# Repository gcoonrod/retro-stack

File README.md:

# retro-stack

A retro computer project based on stackable PCB boards. This project was largely inspired by Ben Eater's 6502 breadboard computer project.

## Project Objective

Design, prototype, and build an 8 bit computer roughly comparable to an Apple II or NES in capabilities.

### Hardware Design Goals

Create an 8 bit computer with the following basic capabilities:

- Stable at or near maximum frequency of the processor
- Modular (including reconfigurable address map)
- Character display via RS-232 Serial and LCD
- PS/2 Keyboard Input

Optional:

- Sound generation
- VGA video output
- 10baseT ethernet

### Software Design Goals

- Develop a strong understanding of Assembly programming
- Understand and implement the following protocols:
  - UART
  - SPI
  - PS/2
- Learn the basics of PLDs and CUPL to use in "glue logic"
- Develop a moderate to strong understanding of Atmel AVR MCU programming
- Implement a simple Operating System within the constraints of an 8 bit architecture
- Understand and implement both software and hardware interrupts

## Repository Layout

This repository contains all of the hardware and software assets in the following structure:

- [Hardware Schematics and PCB Layouts](./boards/)
- [Firmware](./firmware/)
- Tooling (TBD)
- Documentation (TBD)s

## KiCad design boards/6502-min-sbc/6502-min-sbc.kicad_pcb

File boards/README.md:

<!--
 Copyright 2023 Greg Coonrod
 
 Licensed under the Apache License, Version 2.0 (the "License");
 you may not use this file except in compliance with the License.
 You may obtain a copy of the License at
 
     http://www.apache.org/licenses/LICENSE-2.0
 
 Unless required by applicable law or agreed to in writing, software
 distributed under the License is distributed on an "AS IS" BASIS,
 WITHOUT WARRANTIES OR CONDITIONS OF ANY KIND, either express or implied.
 See the License for the specific language governing permissions and
 limitations under the License.
-->

# RetroStack - Boards

The RetroStack project currently includes the following boards based on a common [template](./retro-stack-template/):

- [Power Supply & 555 Clock](./retro-stack-power-clock/)
- [W65C02S CPU & High Speed Clock](./retro-stack-cpu/)
- [SRAM & ROM](./retro-stack-ram-rom/)
- [Arduino Mega Debug Shield](./retro-stack-debug-arduino-mega-shield/)
- [Debug & Status Display](./retro-stack-debug/)

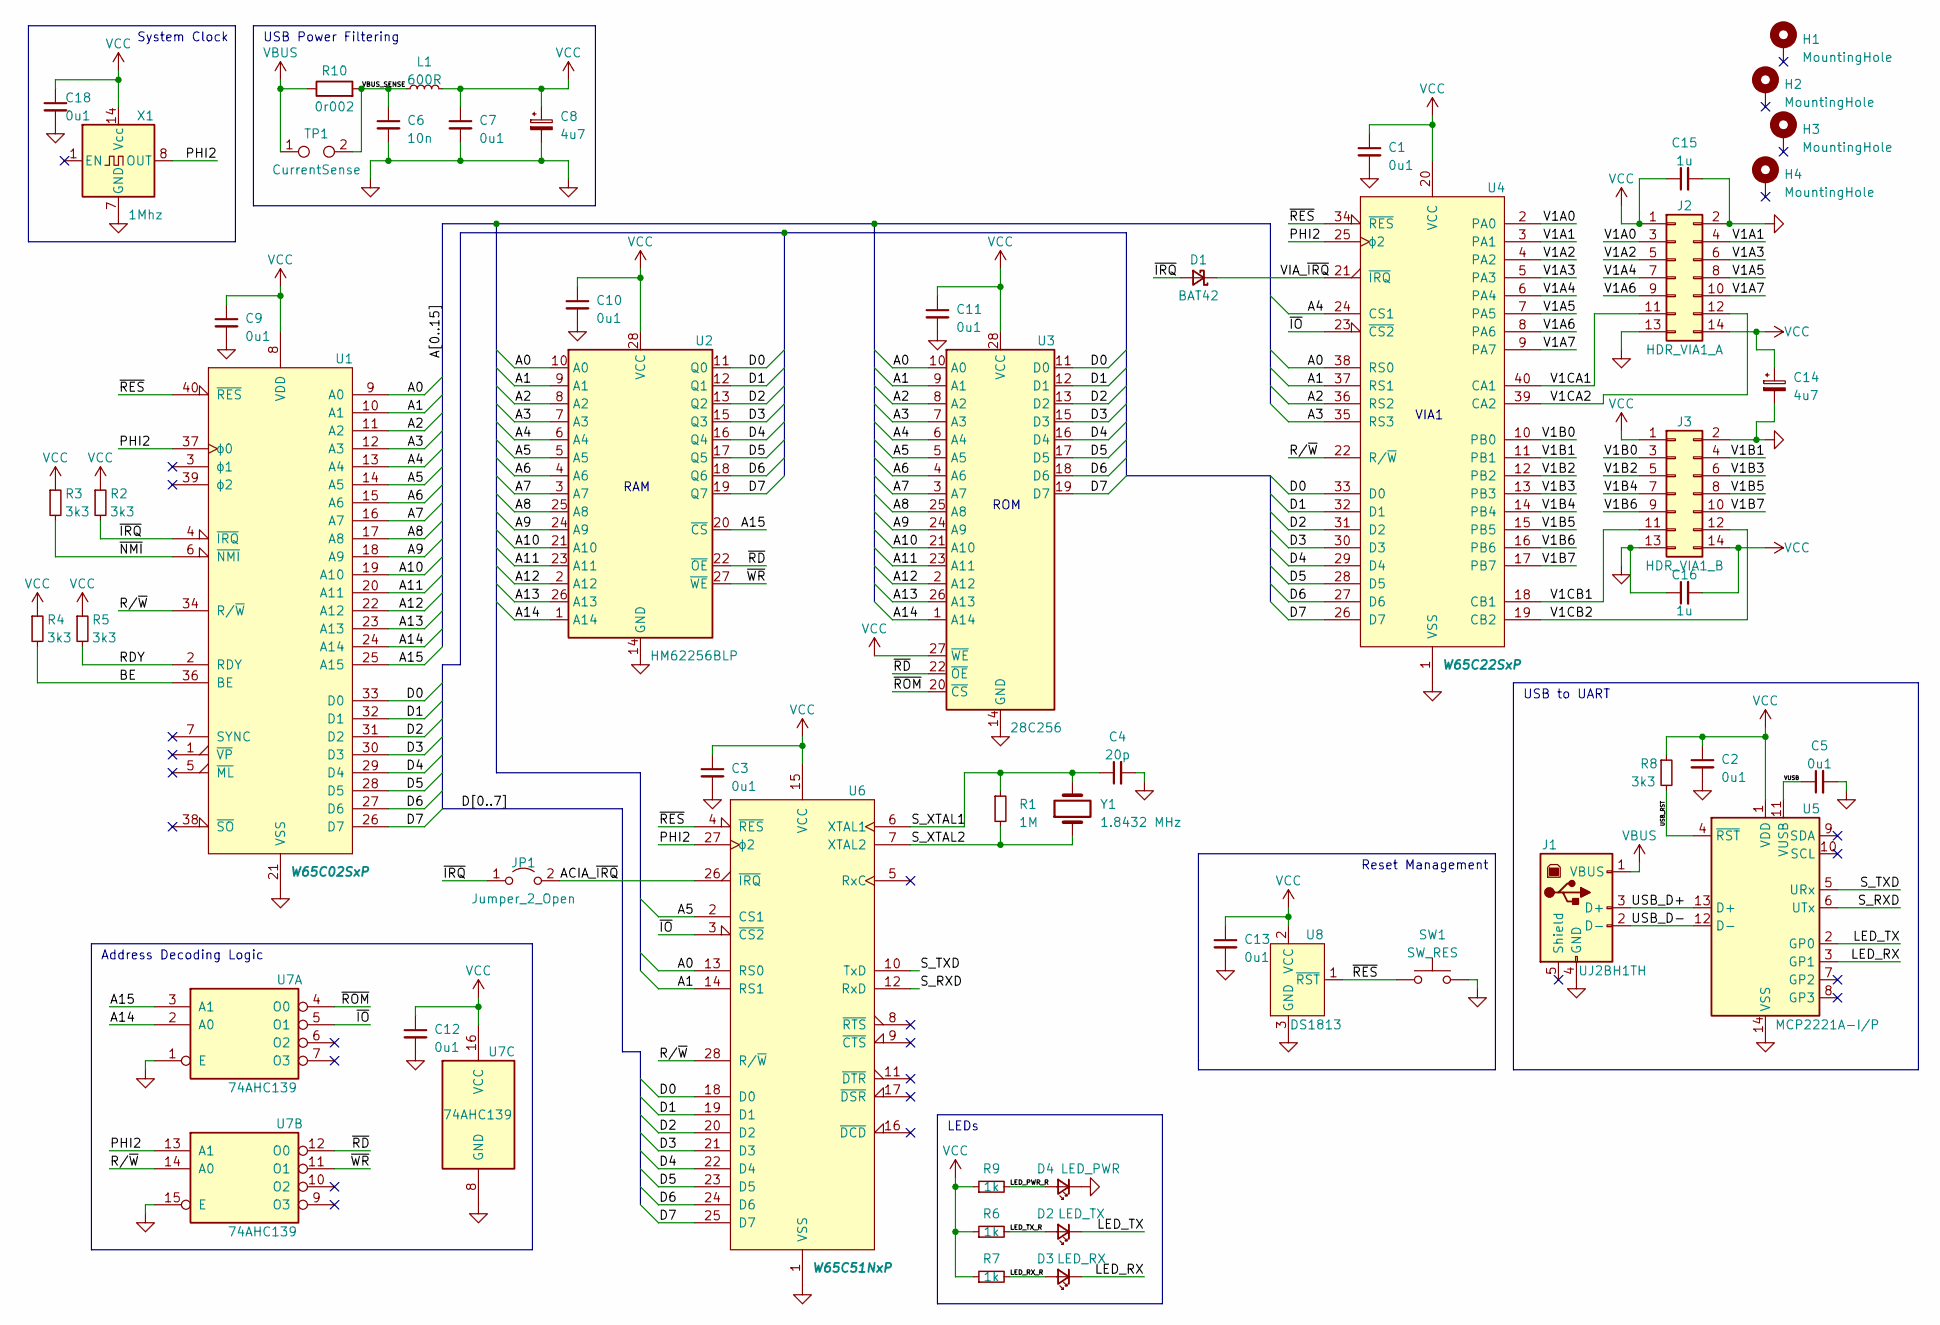
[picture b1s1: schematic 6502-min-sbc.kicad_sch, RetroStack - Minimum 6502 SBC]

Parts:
C1, C2, C3, C5, C7, C9, C10, C11, C12, C13, C18: 0u1; C_Rect_L4.0mm_W2.5mm_P2.50mm; Manufacturer Part K104K15X7RF5TL2
C4: 20p; C_Rect_L4.6mm_W3.8mm_P2.50mm_MKS02_FKP02; Manufacturer Part C315C200J3G5TA
C6: 10n; C_Rect_L4.0mm_W2.5mm_P2.50mm; Manufacturer Part K103K10X7RF53L2
C8, C14: 4u7; CP_Radial_D5.0mm_P2.50mm; Manufacturer Part ECE-A1VKS4R7I
C15, C16: 1u; C_Rect_L4.6mm_W3.0mm_P2.50mm_MKS02_FKP02; Manufacturer Part FG18X7R1E105KRT06
D1: BAT42; D_DO-35_SOD27_P7.62mm_Horizontal; Manufacturer Part BAT42
D2: LED_TX; LED_D5.0mm; Manufacturer Part WP7113YT
D3: LED_RX; LED_D5.0mm; Manufacturer Part WP7113YT
D4: LED_PWR; LED_D5.0mm; Manufacturer Part WP7113YT
H1, H2, H3, H4: MountingHole; MountingHole_3.2mm_M3_Pad
J1: UJ2BH1TH; Manufacturer Part UJ2-BH-1-TH
J2: HDR_VIA1_A; IDC-Header_2x07_P2.54mm_Vertical; Manufacturer Part 61201421621
J3: HDR_VIA1_B; IDC-Header_2x07_P2.54mm_Vertical; Manufacturer Part 61201421621
JP1: Jumper_2_Open; PinHeader_1x02_P2.54mm_Vertical
L1: 600R; LairdTech_28C0236-0JW-10; Manufacturer Part 28C0236-0JW-10
R1: 1M; R_Axial_DIN0204_L3.6mm_D1.6mm_P5.08mm_Horizontal; Manufacturer Part MBA02040C1004FCT00
R2, R3, R4, R5, R8: 3k3; R_Axial_DIN0204_L3.6mm_D1.6mm_P5.08mm_Horizontal; Manufacturer Part MBA02040C3301FCT00
R6, R7, R9: 1k; R_Axial_DIN0204_L3.6mm_D1.6mm_P5.08mm_Horizontal; Manufacturer Part MBA02040C1001FCT00
R10: 0r002; RESC6430X38N; Manufacturer Part WSLF25122L000FEA
SW1: SW_RES; SW_PUSH_6mm
TP1: CurrentSense; TestPoint_2Pads_Pitch2.54mm_Drill0.8mm
U1: W65C02SxP; DIP-40_W15.24mm_Socket_LongPads; Manufacturer Part W65C02S6TPG-14
U2: HM62256BLP; DIP-28_W15.24mm_Socket_LongPads; Manufacturer Part AS6C62256-55PCN
U3: 28C256; 28655410; Manufacturer Part AT28C256-15PU
U4: W65C22SxP; DIP-40_W15.24mm_Socket_LongPads; Manufacturer Part W65C22S6TPG-14
U5: MCP2221A-I/P; DIP-14_W7.62mm_Socket_LongPads; Manufacturer Part MCP2221A-I/P
U6: W65C51NxP; DIP-28_W15.24mm_Socket_LongPads; Manufacturer Part W65C51N6TPG-14
U7: 74AHC139; DIP-16_W7.62mm_Socket_LongPads; Manufacturer Part SN74AHC139N
U8: DS1813; TO-92; Manufacturer Part DS1813-15+
X1: 1Mhz; Oscillator_DIP-14; Manufacturer Part MXO45T-2C-1M0000
Y1: 1.8432 MHz; Crystal_HC49-U_Vertical; Manufacturer Part AB-1.8432MHZ-B2

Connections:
/A0: U1.9 (A0), U2.10 (A0), U3.10 (A0), U4.38 (RS0), U6.13 (RS0)
/A1: U1.10 (A1), U2.9 (A1), U3.9 (A1), U4.37 (RS1), U6.14 (RS1)
/A2: U1.11 (A2), U2.8 (A2), U3.8 (A2), U4.36 (RS2)
/A3: U1.12 (A3), U2.7 (A3), U3.7 (A3), U4.35 (RS3)
/A4: U1.13 (A4), U2.6 (A4), U3.6 (A4), U4.24 (CS1)
/A5: U1.14 (A5), U2.5 (A5), U3.5 (A5), U6.2 (CS1)
/A6: U1.15 (A6), U2.4 (A6), U3.4 (A6)
/A7: U1.16 (A7), U2.3 (A7), U3.3 (A7)
/A8: U1.17 (A8), U2.25 (A8), U3.25 (A8)
/A9: U1.18 (A9), U2.24 (A9), U3.24 (A9)
/A10: U1.19 (A10), U2.21 (A10), U3.21 (A10)
/A11: U1.20 (A11), U2.23 (A11), U3.23 (A11)
/A12: U1.22 (A12), U2.2 (A12), U3.2 (A12)
/A13: U1.23 (A13), U2.26 (A13), U3.26 (A13)
/A14: U1.24 (A14), U2.1 (A14), U3.1 (A14), U7.2 (A0)
/A15: U1.25 (A15), U2.20 (~CS), U7.3 (A1)
/ACIA_~IRQ: JP1.2 (B), U6.26 (~IRQ)
/BE: R4.2, U1.36 (BE)
/D0: U1.33 (D0), U2.11 (Q0), U3.11 (D0), U4.33 (D0), U6.18 (D0)
/D1: U1.32 (D1), U2.12 (Q1), U3.12 (D1), U4.32 (D1), U6.19 (D1)
/D2: U1.31 (D2), U2.13 (Q2), U3.13 (D2), U4.31 (D2), U6.20 (D2)
/D3: U1.30 (D3), U2.15 (Q3), U3.15 (D3), U4.30 (D3), U6.21 (D3)
/D4: U1.29 (D4), U2.16 (Q4), U3.16 (D4), U4.29 (D4), U6.22 (D4)
/D5: U1.28 (D5), U2.17 (Q5), U3.17 (D5), U4.28 (D5), U6.23 (D5)
/D6: U1.27 (D6), U2.18 (Q6), U3.18 (D6), U4.27 (D6), U6.24 (D6)
/D7: U1.26 (D7), U2.19 (Q7), U3.19 (D7), U4.26 (D7), U6.25 (D7)
/LED_PWR_R: D4.2 (A), R9.2
/LED_RX: D3.1 (K), U5.3 (GP1)
/LED_RX_R: D3.2 (A), R7.2
/LED_TX: D2.1 (K), U5.2 (GP0)
/LED_TX_R: D2.2 (A), R6.2
/PHI2: U1.37 (ϕ0), U4.25 (ϕ2), U6.27 (ϕ2), U7.13 (A1), X1.8 (OUT)
/RDY: R5.2, U1.2 (RDY)
/R/~W: U1.34 (R/~W), U4.22 (R/~W), U6.28 (R/~W), U7.14 (A0)
/S_RXD: U5.6 (UTx), U6.12 (RxD)
/S_TXD: U5.5 (URx), U6.10 (TxD)
/S_XTAL1: C4.1, R1.1, U6.6 (XTAL1), Y1.2
/S_XTAL2: R1.2, U6.7 (XTAL2), Y1.1
/USB_D+: J1.3 (D+), U5.13 (D+)
/USB_D-: J1.2 (D-), U5.12 (D-)
/USB_RST: R8.2, U5.4 (~RST)
/V1A0: J2.3, U4.2 (PA0)
/V1A1: J2.4, U4.3 (PA1)
/V1A2: J2.5, U4.4 (PA2)
/V1A3: J2.6, U4.5 (PA3)
/V1A4: J2.7, U4.6 (PA4)
/V1A5: J2.8, U4.7 (PA5)
/V1A6: J2.9, U4.8 (PA6)
/V1A7: J2.10, U4.9 (PA7)
/V1B0: J3.3, U4.10 (PB0)
/V1B1: J3.4, U4.11 (PB1)
/V1B2: J3.5, U4.12 (PB2)
/V1B3: J3.6, U4.13 (PB3)
/V1B4: J3.7, U4.14 (PB4)
/V1B5: J3.8, U4.15 (PB5)
/V1B6: J3.9, U4.16 (PB6)
/V1B7: J3.10, U4.17 (PB7)
/V1CA1: J2.11, U4.40 (CA1)
/V1CA2: J2.12, U4.39 (CA2)
/V1CB1: J3.11, U4.18 (CB1)
/V1CB2: J3.12, U4.19 (CB2)
/VBUS_SENSE: C6.1, L1.1, R10.2, TP1.2
/VIA_~IRQ: D1.1 (K), U4.21 (~IRQ)
/VUSB: C5.1, U5.11 (VUSB)
/~IO: U4.23 (~CS2), U6.3 (~CS2), U7.5 (O1)
/~IRQ: D1.2 (A), JP1.1 (A), R2.2, U1.4 (~IRQ)
/~NMI: R3.2, U1.6 (~NMI)
/~RD: U2.22 (~OE), U3.22 (~OE), U7.12 (O0)
/~RES: SW1.1, U1.40 (~RES), U4.34 (~RES), U6.4 (~RES), U8.1 (~RST)
/~ROM: U3.20 (~CS), U7.4 (O0)
/~WR: U2.27 (~WE), U7.11 (O1)
GND: C1.2, C2.2, C3.2, C4.2, C5.2, C6.2, C7.2, C8.2, C9.2, C10.2, C11.2, C12.2, C13.2, C14.2, C15.2, C16.1, C18.2, D4.1 (K), J1.4 (GND), J2.2, J2.13, J3.2, J3.13, SW1.2, U1.21 (VSS), U2.14 (GND), U3.14 (GND), U4.1 (VSS), U5.14 (VSS), U6.1 (VSS), U7.1 (E), U7.8 (GND), U7.15 (E), U8.3 (GND), X1.7 (GND)
VBUS: J1.1 (VBUS), R10.1, TP1.1
VCC: C1.1, C2.1, C3.1, C7.1, C8.1, C9.1, C10.1, C11.1, C12.1, C13.1, C14.1, C15.1, C16.2, C18.1, J2.1, J2.14, J3.1, J3.14, L1.2, R2.1, R3.1, R4.1, R5.1, R6.1, R7.1, R8.1, R9.1, U1.8 (VDD), U2.28 (VCC), U3.27 (~WE), U3.28 (VCC), U4.20 (VCC), U5.1 (VDD), U6.15 (VCC), U7.16 (VCC), U8.2 (VCC), X1.14 (Vcc)

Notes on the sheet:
LEDs
System Clock
USB to UART
USB Power Filtering
ROM
Address Decoding Logic
Reset Management
VIA1
RAM

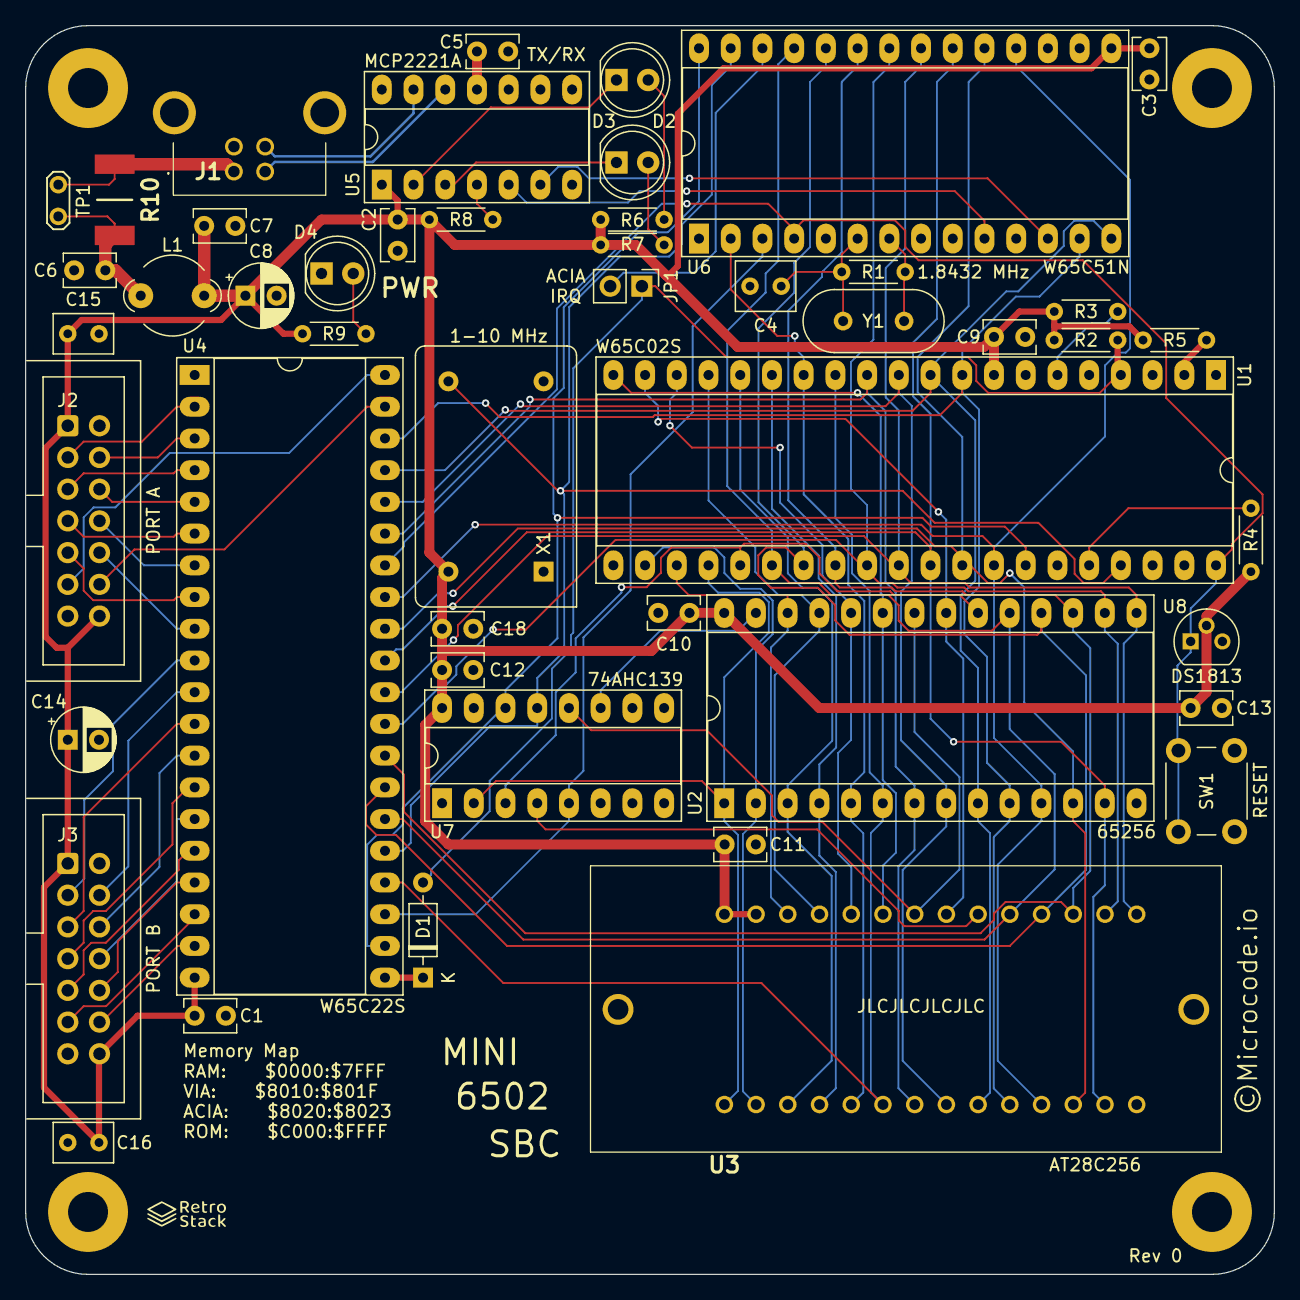
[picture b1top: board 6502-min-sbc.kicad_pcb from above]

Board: 4 copper layers, 100.0 x 100.0 mm, 52 parts (0 on the bottom side), 74 nets.

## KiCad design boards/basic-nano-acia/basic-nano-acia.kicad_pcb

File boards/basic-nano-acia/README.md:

<!--
 Copyright 2023 Greg Coonrod
 
 Licensed under the Apache License, Version 2.0 (the "License");
 you may not use this file except in compliance with the License.
 You may obtain a copy of the License at
 
     http://www.apache.org/licenses/LICENSE-2.0
 
 Unless required by applicable law or agreed to in writing, software
 distributed under the License is distributed on an "AS IS" BASIS,
 WITHOUT WARRANTIES OR CONDITIONS OF ANY KIND, either express or implied.
 See the License for the specific language governing permissions and
 limitations under the License.
-->

# RetroStack - Basic Nano ACIA

A semi-compatible DIP-28 clone of the 6551 ACIA.

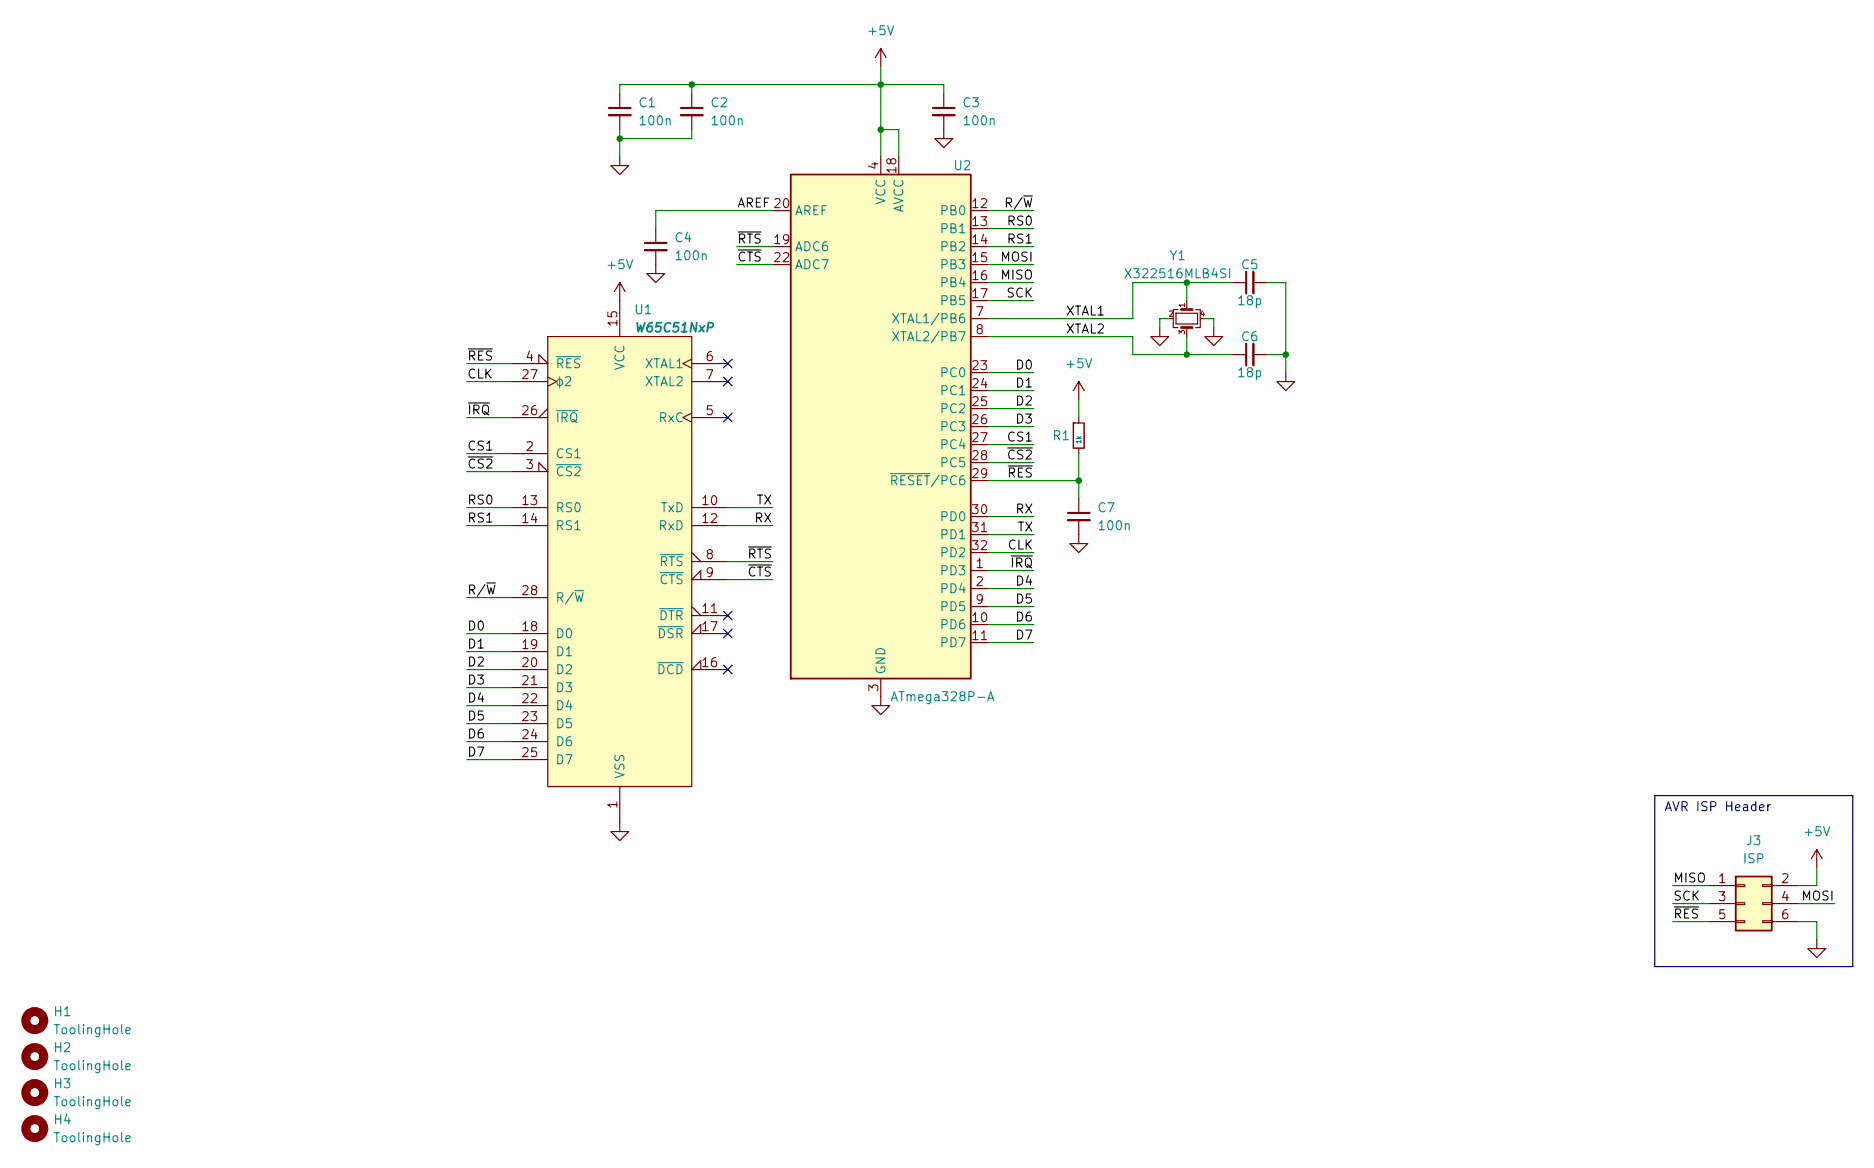
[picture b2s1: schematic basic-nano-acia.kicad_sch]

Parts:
C1, C2, C3, C4, C7: 100n; C_0402_1005Metric; Mfr Part CL05B104KO5NNNC
C5, C6: 18p; C_0402_1005Metric; Mfr Part 0402CG180J500NT
H1, H2, H3, H4: ToolingHole; ToolingHole_JLCPCB
J3: ISP; PinHeader_2x03_P2.54mm_Vertical
R1: 1k; R_0402_1005Metric; Mfr Part 0402WGF1001TCE
U1: W65C51NxP; DIP-28_W15.24mm
U2: ATmega328P-A; TQFP-32_7x7mm_P0.8mm; Mfr Part ATMEGA328P-AU
Y1: X322516MLB4SI; Crystal_SMD_EuroQuartz_MT-4Pin_3.2x2.5mm; Mfr Part X322516MLB4SI

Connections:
+5V: C1.1, C2.1, C3.1, J3.2, R1.1, U1.15 (VCC), U2.4 (VCC), U2.6 (VCC), U2.18 (AVCC)
/AREF: C4.1, U2.20 (AREF)
/CLK: U1.27 (ϕ2), U2.32 (PD2)
/CS1: U1.2 (CS1), U2.27 (PC4)
/D0: U1.18 (D0), U2.23 (PC0)
/D1: U1.19 (D1), U2.24 (PC1)
/D2: U1.20 (D2), U2.25 (PC2)
/D3: U1.21 (D3), U2.26 (PC3)
/D4: U1.22 (D4), U2.2 (PD4)
/D5: U1.23 (D5), U2.9 (PD5)
/D6: U1.24 (D6), U2.10 (PD6)
/D7: U1.25 (D7), U2.11 (PD7)
/MISO: J3.1, U2.16 (PB4)
/MOSI: J3.4, U2.15 (PB3)
/RS0: U1.13 (RS0), U2.13 (PB1)
/RS1: U1.14 (RS1), U2.14 (PB2)
/RX: U1.12 (RxD), U2.30 (PD0)
/R/~W: U1.28 (R/~W), U2.12 (PB0)
/SCK: J3.3, U2.17 (PB5)
/TX: U1.10 (TxD), U2.31 (PD1)
/XTAL1: C5.1, U2.7 (XTAL1/PB6), Y1.1
/XTAL2: C6.1, U2.8 (XTAL2/PB7), Y1.3
/~CS2: U1.3 (~CS2), U2.28 (PC5)
/~CTS: U1.9 (~CTS), U2.22 (ADC7)
/~IRQ: U1.26 (~IRQ), U2.1 (PD3)
/~RES: C7.1, J3.5, R1.2, U1.4 (~RES), U2.29 (~RESET/PC6)
/~RTS: U1.8 (~RTS), U2.19 (ADC6)
GND: C1.2, C2.2, C3.2, C4.2, C5.2, C6.2, C7.2, J3.6, U1.1 (VSS), U2.3 (GND), U2.5 (GND), U2.21 (GND), Y1.2, Y1.4

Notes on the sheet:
AVR ISP Header

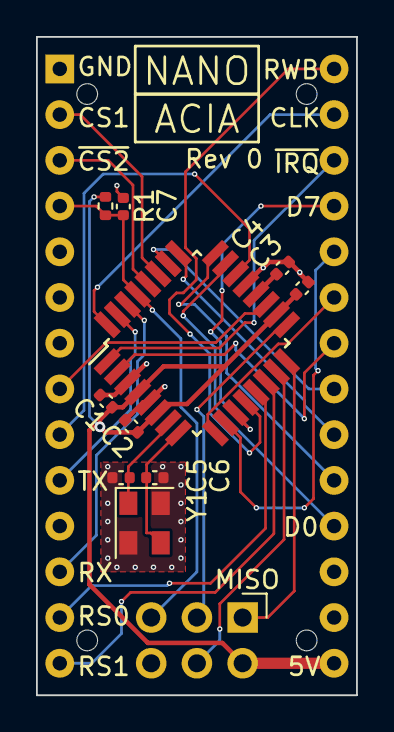
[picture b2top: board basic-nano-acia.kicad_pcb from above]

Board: 4 copper layers, 17.8 x 36.6 mm, 16 parts (0 on the bottom side), 28 nets.

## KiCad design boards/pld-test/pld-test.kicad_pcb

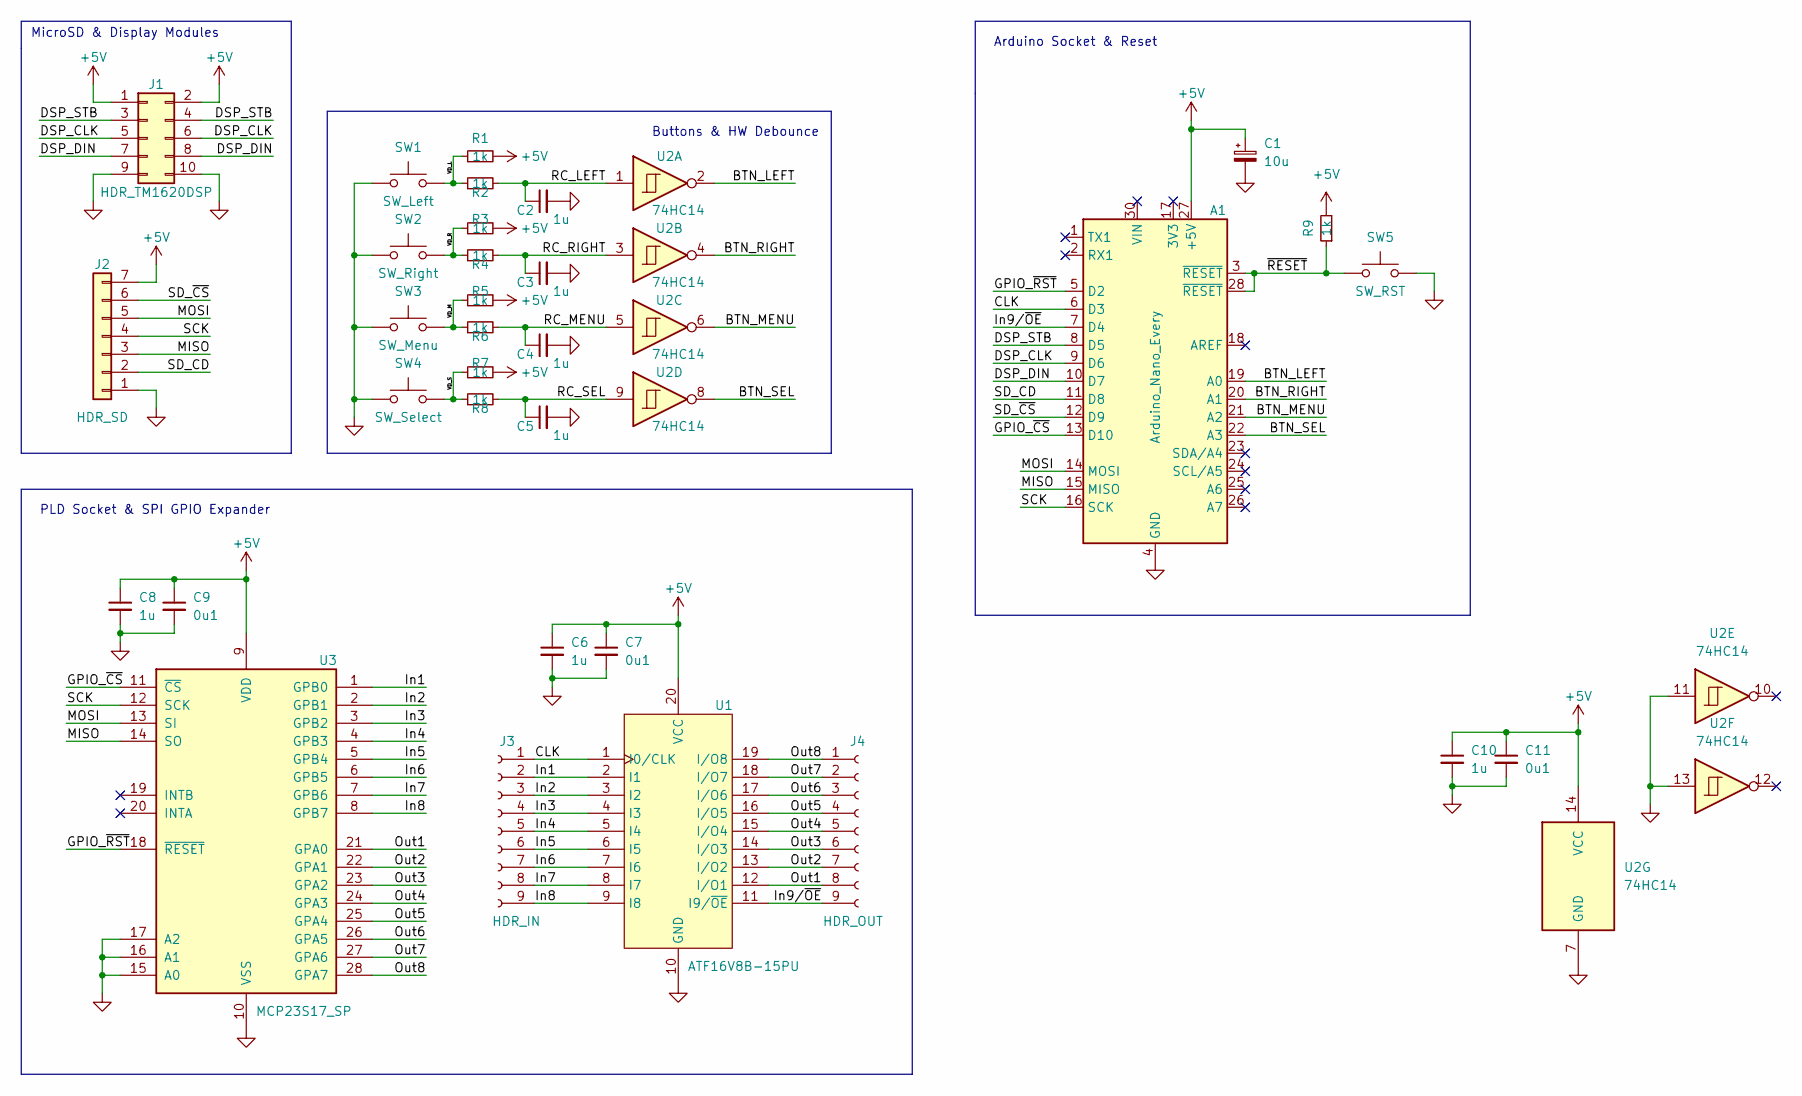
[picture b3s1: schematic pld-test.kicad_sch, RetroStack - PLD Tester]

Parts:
A1: Arduino_Nano_Every; Arduino_Nano; Man Part # ABX00028
C1: 10u; CP_Radial_D5.0mm_P2.50mm; Man Part # ECE-A1EKS100I
C2, C3, C4, C5, C6, C8, C10: 1u; C_Rect_L4.0mm_W2.5mm_P2.50mm; Man Part # FA18X7R1E105KRU06
C7, C9, C11: 0u1; C_Rect_L4.0mm_W2.5mm_P2.50mm; Man Part # K104K15X7RF5TL2
J1: HDR_TM1620DSP; PinHeader_2x05_P2.54mm_Vertical
J2: HDR_SD; PinHeader_1x07_P2.54mm_Vertical; Man Part # DEV-13743
J3: HDR_IN; PinSocket_1x09_P2.54mm_Vertical; Man Part # 310-87-109-41-001101
J4: HDR_OUT; PinSocket_1x09_P2.54mm_Vertical; Man Part # 310-87-109-41-001101
R1, R2, R3, R4, R5, R6, R7, R8, R9: 1k; R_Axial_DIN0204_L3.6mm_D1.6mm_P5.08mm_Horizontal; Man Part # MBA02040C1001FCT00
SW1: SW_Left; SW_PUSH_6mm; Man Part # TS02-66-43-BK-260-LCR-D
SW2: SW_Right; SW_PUSH_6mm; Man Part # TS02-66-43-BK-260-LCR-D
SW3: SW_Menu; SW_PUSH_6mm; Man Part # TS02-66-43-BK-260-LCR-D
SW4: SW_Select; SW_PUSH_6mm; Man Part # TS02-66-43-BK-260-LCR-D
SW5: SW_RST; SW_PUSH_6mm; Man Part # TS02-66-43-BK-260-LCR-D
U1: ATF16V8B-15PU; DIP-20_W7.62mm_Socket_LongPads; Man Part # ATF16V8B-15PU
U2: 74HC14; DIP-14_W7.62mm_Socket_LongPads; Man Part # SN74HC14N
U3: MCP23S17_SP; DIP-28_W7.62mm_Socket_LongPads; Man Part # MCP23S17-E/SP

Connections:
+5V: A1.27 (+5V), C1.1, C6.1, C7.1, C8.1, C9.1, C10.1, C11.1, J1.1, J1.2, J2.7, R1.2, R3.2, R5.2, R7.2, R9.2, U1.20 (VCC), U2.14 (VCC), U3.9 (VDD)
/BTN_LEFT: A1.19 (A0), U2.2
/BTN_MENU: A1.21 (A2), U2.6
/BTN_RIGHT: A1.20 (A1), U2.4
/BTN_SEL: A1.22 (A3), U2.8
/CLK: A1.6 (D3), J3.1, U1.1 (I0/CLK)
/DSP_CLK: A1.9 (D6), J1.5, J1.6
/DSP_DIN: A1.10 (D7), J1.7, J1.8
/DSP_STB: A1.8 (D5), J1.3, J1.4
/GPIO_~CS: A1.13 (D10), U3.11 (~CS)
/GPIO_~RST: A1.5 (D2), U3.18 (~RESET)
/In1: J3.2, U1.2 (I1), U3.1 (GPB0)
/In2: J3.3, U1.3 (I2), U3.2 (GPB1)
/In3: J3.4, U1.4 (I3), U3.3 (GPB2)
/In4: J3.5, U1.5 (I4), U3.4 (GPB3)
/In5: J3.6, U1.6 (I5), U3.5 (GPB4)
/In6: J3.7, U1.7 (I6), U3.6 (GPB5)
/In7: J3.8, U1.8 (I7), U3.7 (GPB6)
/In8: J3.9, U1.9 (I8), U3.8 (GPB7)
/In9/~OE: A1.7 (D4), J4.9, U1.11 (I9/~OE)
/MISO: A1.15 (MISO), J2.3, U3.14 (SO)
/MOSI: A1.14 (MOSI), J2.5, U3.13 (SI)
/Out1: J4.8, U1.12 (I/O1), U3.21 (GPA0)
/Out2: J4.7, U1.13 (I/O2), U3.22 (GPA1)
/Out3: J4.6, U1.14 (I/O3), U3.23 (GPA2)
/Out4: J4.5, U1.15 (I/O4), U3.24 (GPA3)
/Out5: J4.4, U1.16 (I/O5), U3.25 (GPA4)
/Out6: J4.3, U1.17 (I/O6), U3.26 (GPA5)
/Out7: J4.2, U1.18 (I/O7), U3.27 (GPA6)
/Out8: J4.1, U1.19 (I/O8), U3.28 (GPA7)
/RC_LEFT: C2.1, R2.2, U2.1
/RC_MENU: C4.1, R6.2, U2.5
/RC_RIGHT: C3.1, R4.2, U2.3
/RC_SEL: C5.1, R8.2, U2.9
/SCK: A1.16 (SCK), J2.4, U3.12 (SCK)
/SD_CD: A1.11 (D8), J2.2
/SD_~CS: A1.12 (D9), J2.6
/VD_L: R1.1, R2.1, SW1.2
/VD_M: R5.1, R6.1, SW3.2
/VD_R: R3.1, R4.1, SW2.2
/VD_S: R7.1, R8.1, SW4.2
/~RESET: A1.3 (~RESET), A1.28 (~RESET), R9.1, SW5.1
GND: A1.4 (GND), A1.29 (GND), C1.2, C2.2, C3.2, C4.2, C5.2, C6.2, C7.2, C8.2, C9.2, C10.2, C11.2, J1.9, J1.10, J2.1, SW1.1, SW2.1, SW3.1, SW4.1, SW5.2, U1.10 (GND), U2.7 (GND), U2.11, U2.13, U3.10 (VSS), U3.15 (A0), U3.16 (A1), U3.17 (A2)

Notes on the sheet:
MicroSD & Display Modules
Buttons & HW Debounce
Arduino Socket & Reset
PLD Socket & SPI GPIO Expander

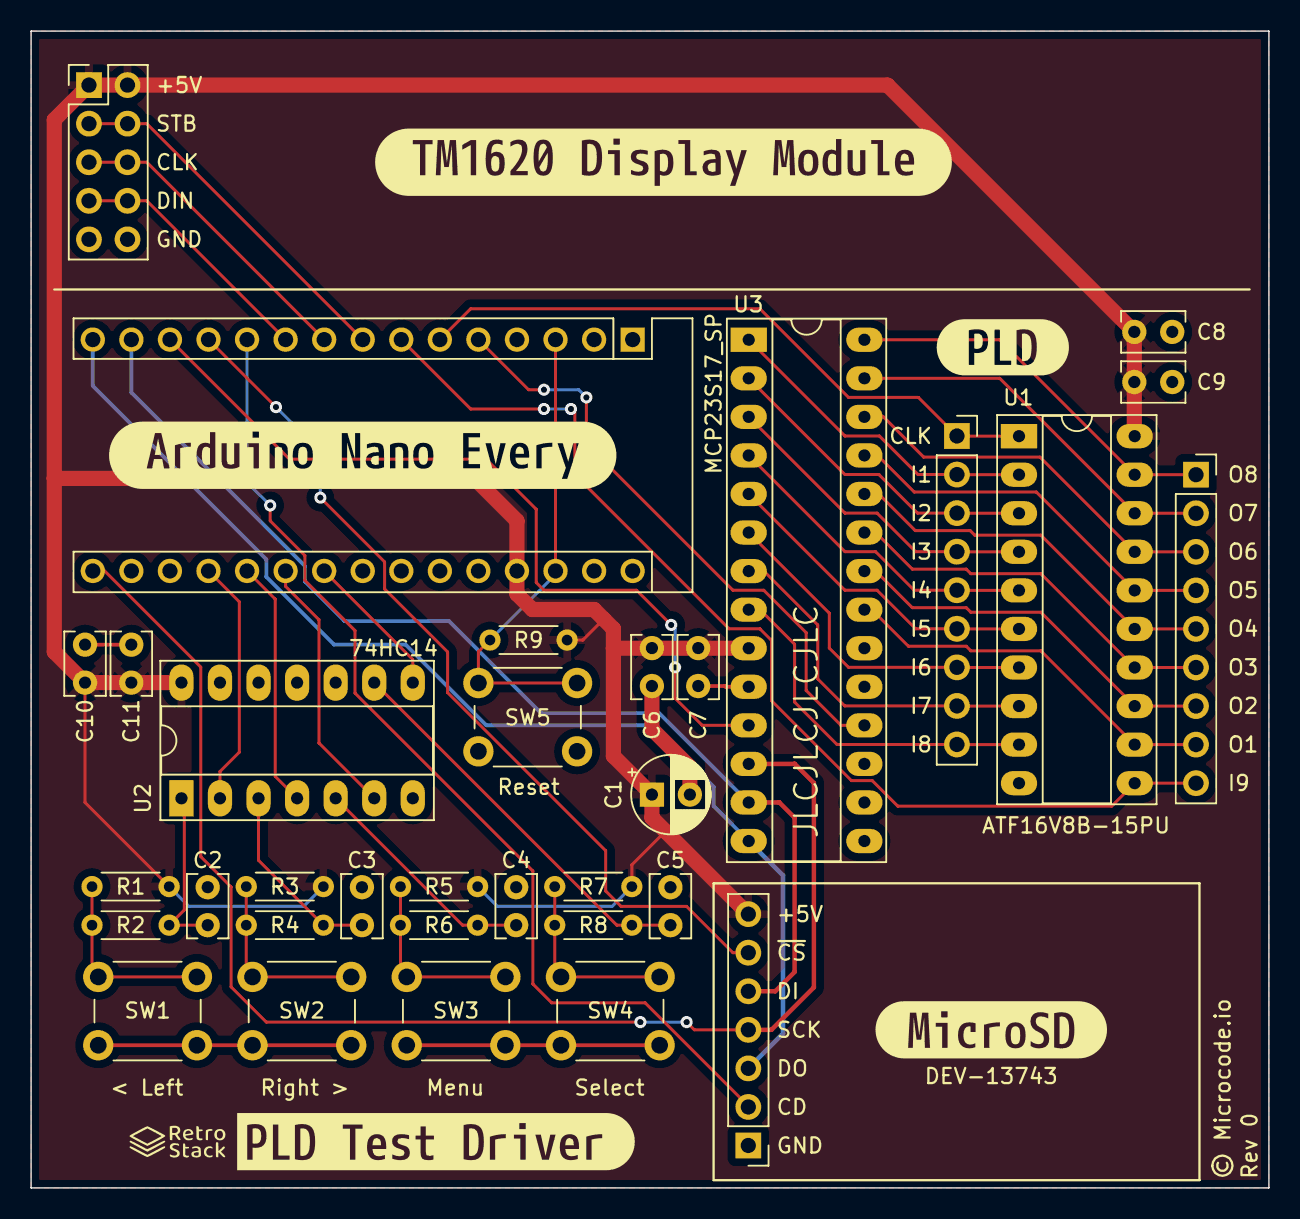
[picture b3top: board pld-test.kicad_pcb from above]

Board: 2 copper layers, 81.5 x 76.2 mm, 38 parts (0 on the bottom side), 43 nets.

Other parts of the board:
kibuzzard-644A8BCE: G***; kibuzzard-644A8BCE
kibuzzard-644A90FB: G***; kibuzzard-644A90FB
kibuzzard-644A91A0: G***; kibuzzard-644A91A0
kibuzzard-644A909B: G***; kibuzzard-644A909B
kibuzzard-644AA1EA: G***; kibuzzard-644AA1EA

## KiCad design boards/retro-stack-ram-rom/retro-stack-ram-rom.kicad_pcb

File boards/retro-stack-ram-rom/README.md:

<!--
 Copyright 2023 Greg Coonrod
 
 Licensed under the Apache License, Version 2.0 (the "License");
 you may not use this file except in compliance with the License.
 You may obtain a copy of the License at
 
     http://www.apache.org/licenses/LICENSE-2.0
 
 Unless required by applicable law or agreed to in writing, software
 distributed under the License is distributed on an "AS IS" BASIS,
 WITHOUT WARRANTIES OR CONDITIONS OF ANY KIND, either express or implied.
 See the License for the specific language governing permissions and
 limitations under the License.
-->

# RetroStack - RAM & ROM Module

This module contains RAM, ROM, and a PLD for address decoding.

## Schematic

Current schematic [pdf](./assets/schematic.pdf).

## PCB Layout & Render

## Known Issues

N/A

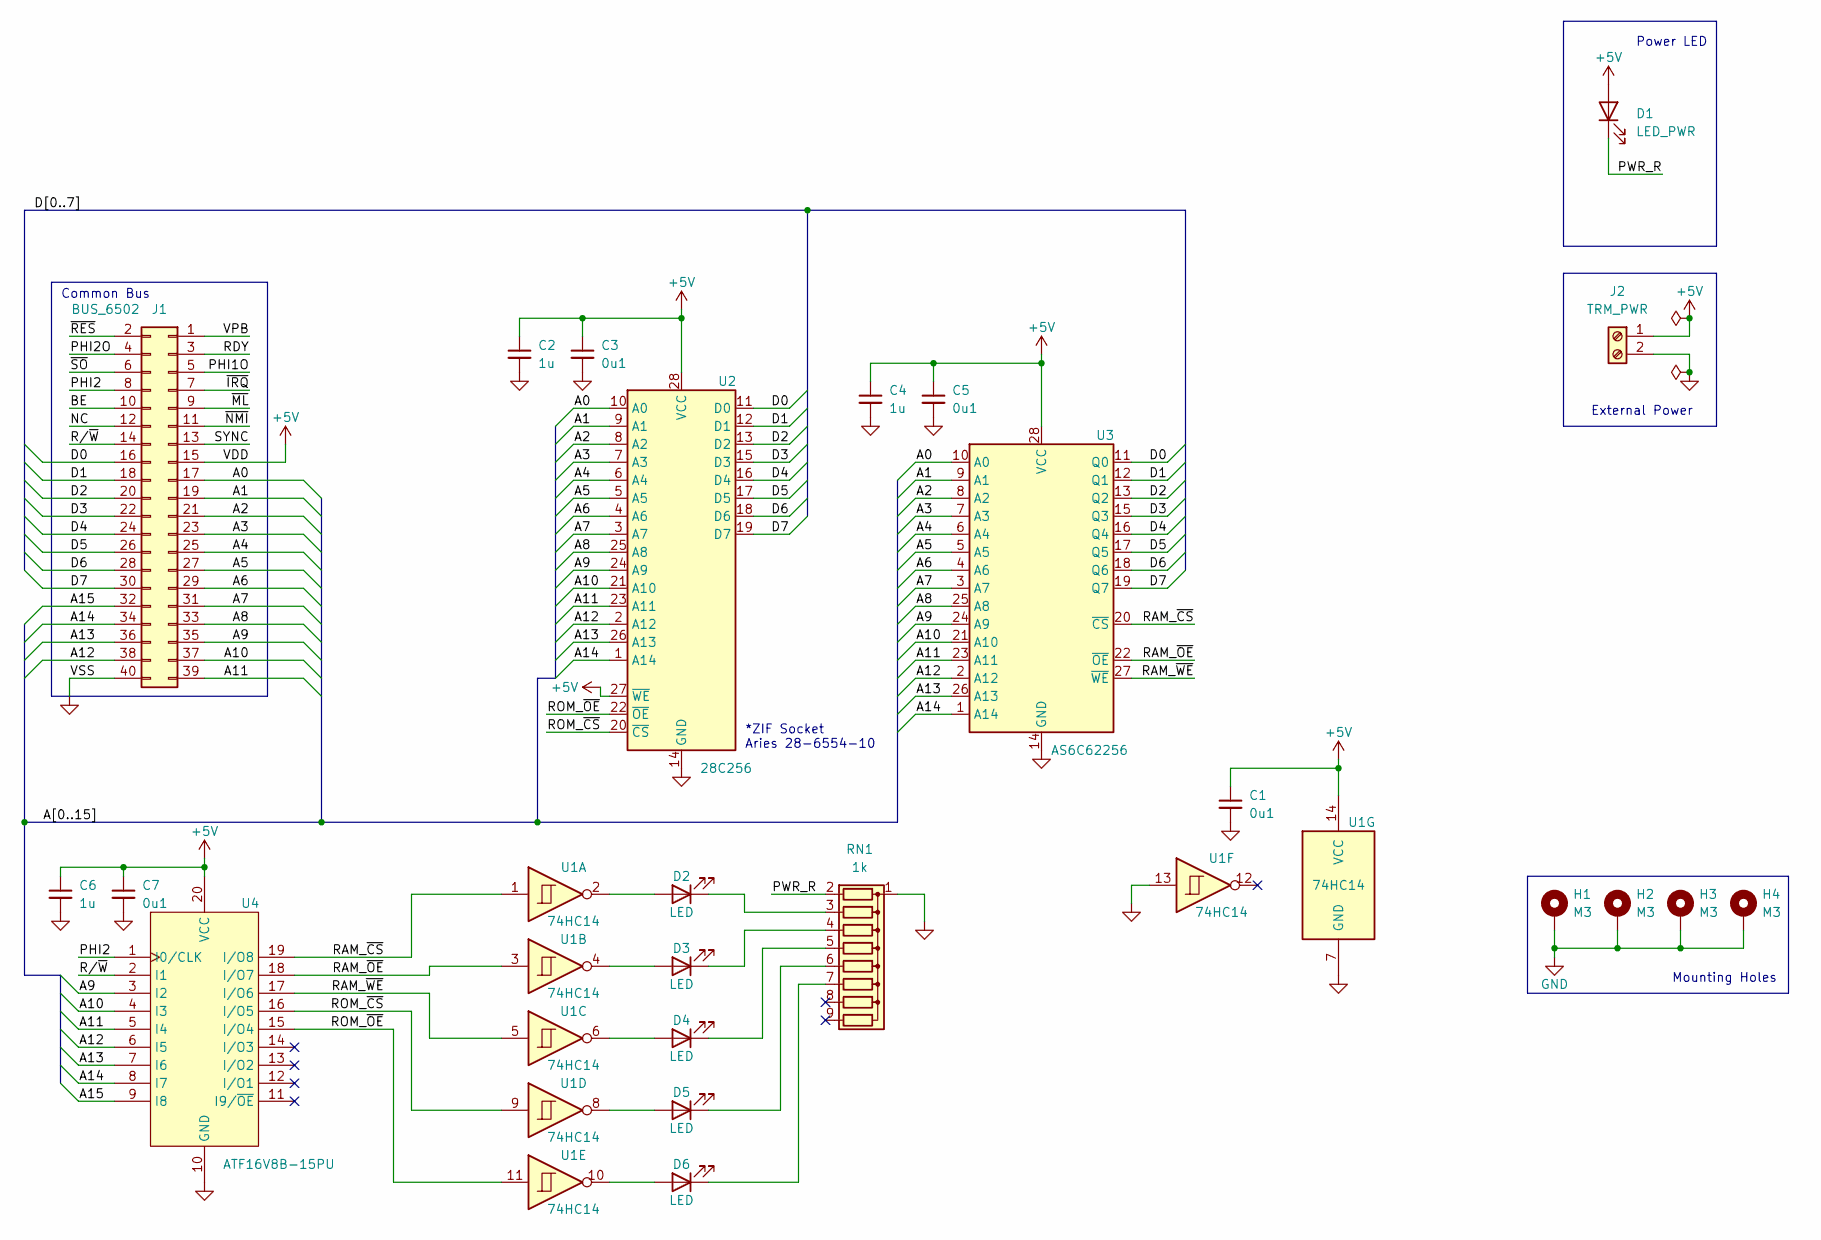
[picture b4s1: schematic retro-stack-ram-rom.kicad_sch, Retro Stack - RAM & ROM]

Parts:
C1, C3, C5, C7: 0u1; C_Rect_L4.0mm_W2.5mm_P2.50mm; Mfr Part RCER71E104K0A2H03B
C2, C4, C6: 1u; C_Rect_L4.0mm_W2.5mm_P2.50mm; Mfr Part FA18X7R1E105KRU06
D1: LED_PWR; LED_D5.0mm
D2, D3, D4, D5, D6: LED; LED_D5.0mm
H1, H2, H3, H4: M3; MountingHole_3.2mm_M3_ISO7380_Pad
J1: BUS_6502; IDC-Header_2x20_P2.54mm_Horizontal; Mfr Part 1979
J2: TRM_PWR; TerminalBlock_Phoenix_MPT-0,5-2-2.54_1x02_P2.54mm_Horizontal; Mfr Part 1725656
RN1: 1k; R_Array_SIP9
U1: 74HC14; DIP-14_W7.62mm_Socket_LongPads
U2: 28C256; 28655410; Mfr Part 28-526-10
U3: AS6C62256; DIP-28_W15.24mm_Socket_LongPads; Mfr Part AS6C62256-55PCN
U4: ATF16V8B-15PU; DIP-20_W7.62mm_Socket_LongPads; Mfr Part ATF16V8B-15PU

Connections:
+5V: C1.1, C2.1, C3.1, C4.1, C5.1, C6.1, C7.1, D1.2 (A), J1.15, J2.1, U1.14 (VCC), U2.27 (~WE), U2.28 (VCC), U3.28 (VCC), U4.20 (VCC)
/A0: J1.17, U2.10 (A0), U3.10 (A0)
/A1: J1.19, U2.9 (A1), U3.9 (A1)
/A2: J1.21, U2.8 (A2), U3.8 (A2)
/A3: J1.23, U2.7 (A3), U3.7 (A3)
/A4: J1.25, U2.6 (A4), U3.6 (A4)
/A5: J1.27, U2.5 (A5), U3.5 (A5)
/A6: J1.29, U2.4 (A6), U3.4 (A6)
/A7: J1.31, U2.3 (A7), U3.3 (A7)
/A8: J1.33, U2.25 (A8), U3.25 (A8)
/A9: J1.35, U2.24 (A9), U3.24 (A9), U4.3 (I2)
/A10: J1.37, U2.21 (A10), U3.21 (A10), U4.4 (I3)
/A11: J1.39, U2.23 (A11), U3.23 (A11), U4.5 (I4)
/A12: J1.38, U2.2 (A12), U3.2 (A12), U4.6 (I5)
/A13: J1.36, U2.26 (A13), U3.26 (A13), U4.7 (I6)
/A14: J1.34, U2.1 (A14), U3.1 (A14), U4.8 (I7)
/A15: J1.32, U4.9 (I8)
/BE: J1.10
/D0: J1.16, U2.11 (D0), U3.11 (Q0)
/D1: J1.18, U2.12 (D1), U3.12 (Q1)
/D2: J1.20, U2.13 (D2), U3.13 (Q2)
/D3: J1.22, U2.15 (D3), U3.15 (Q3)
/D4: J1.24, U2.16 (D4), U3.16 (Q4)
/D5: J1.26, U2.17 (D5), U3.17 (Q5)
/D6: J1.28, U2.18 (D6), U3.18 (Q6)
/D7: J1.30, U2.19 (D7), U3.19 (Q7)
/NC: J1.12
/PHI1O: J1.5
/PHI2: J1.8, U4.1 (I0/CLK)
/PHI2O: J1.4
/PWR_R: D1.1 (K), RN1.2 (R1)
/RAM_~CS: U1.1, U3.20 (~CS), U4.19 (I/O8)
/RAM_~OE: U1.3, U3.22 (~OE), U4.18 (I/O7)
/RAM_~WE: U1.5, U3.27 (~WE), U4.17 (I/O6)
/RDY: J1.3
/ROM_~CS: U1.9, U2.20 (~CS), U4.16 (I/O5)
/ROM_~OE: U1.11, U2.22 (~OE), U4.15 (I/O4)
/R/~W: J1.14, U4.2 (I1)
/SYNC: J1.13
/VPB: J1.1
/~IRQ: J1.7
/~ML: J1.9
/~NMI: J1.11
/~RES: J1.2
/~SO: J1.6
GND: C1.2, C2.2, C3.2, C4.2, C5.2, C6.2, C7.2, H1.1, H2.1, H3.1, H4.1, J1.40, J2.2, RN1.1 (common), U1.7 (GND), U1.13, U2.14 (GND), U3.14 (GND), U4.10 (GND)
unnamed: D2.2 (A), U1.2
unnamed: D3.2 (A), U1.4
unnamed: D4.2 (A), U1.6
unnamed: D5.2 (A), U1.8
unnamed: D6.2 (A), U1.10
unnamed: D2.1 (K), RN1.3 (R2)
unnamed: D3.1 (K), RN1.4 (R3)
unnamed: D4.1 (K), RN1.5 (R4)
unnamed: D5.1 (K), RN1.6 (R5)
unnamed: D6.1 (K), RN1.7 (R6)

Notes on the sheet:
Power LED
External Power
*ZIF Socket Aries 28-6554-10
Common Bus
Mounting Holes

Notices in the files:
boards/6502-min-sbc/6502-min-sbc.kicad_pcb:
©Microcode.io
